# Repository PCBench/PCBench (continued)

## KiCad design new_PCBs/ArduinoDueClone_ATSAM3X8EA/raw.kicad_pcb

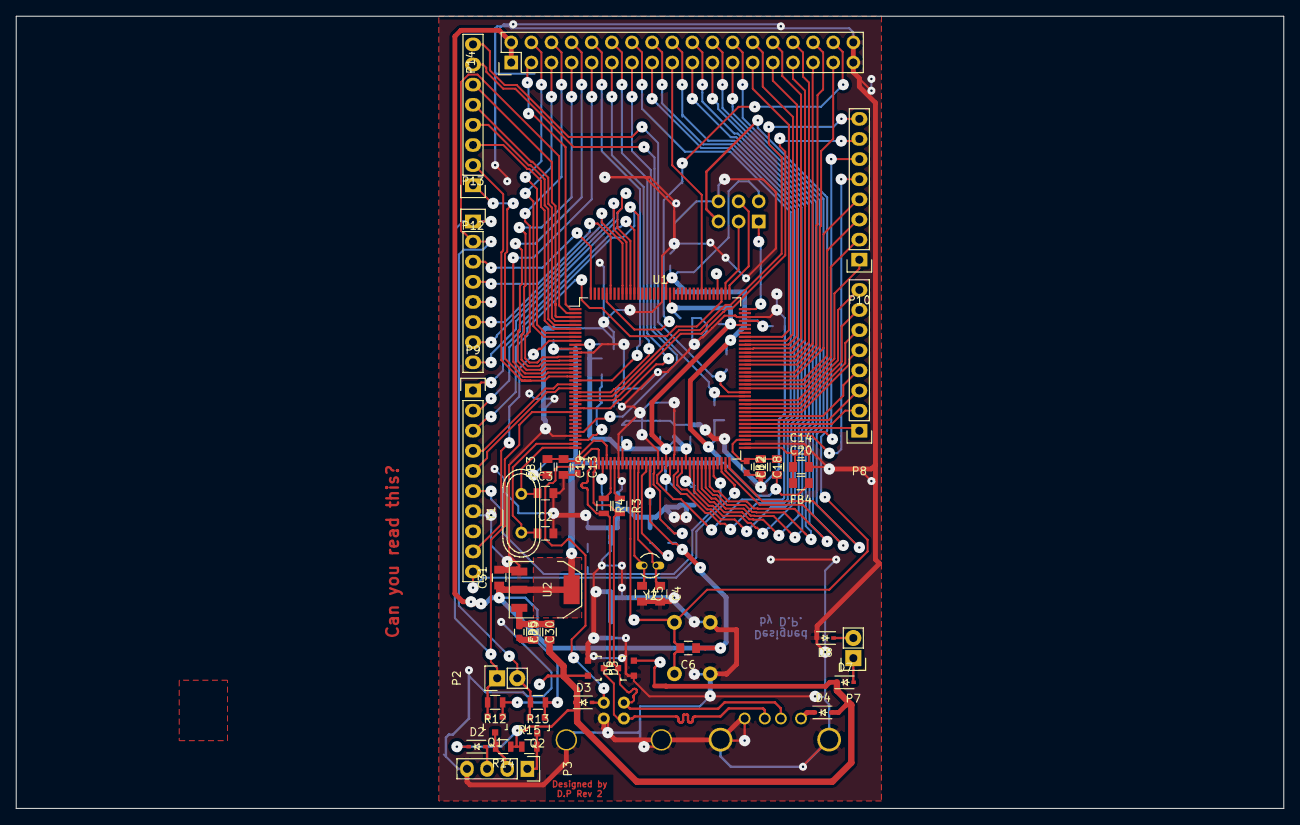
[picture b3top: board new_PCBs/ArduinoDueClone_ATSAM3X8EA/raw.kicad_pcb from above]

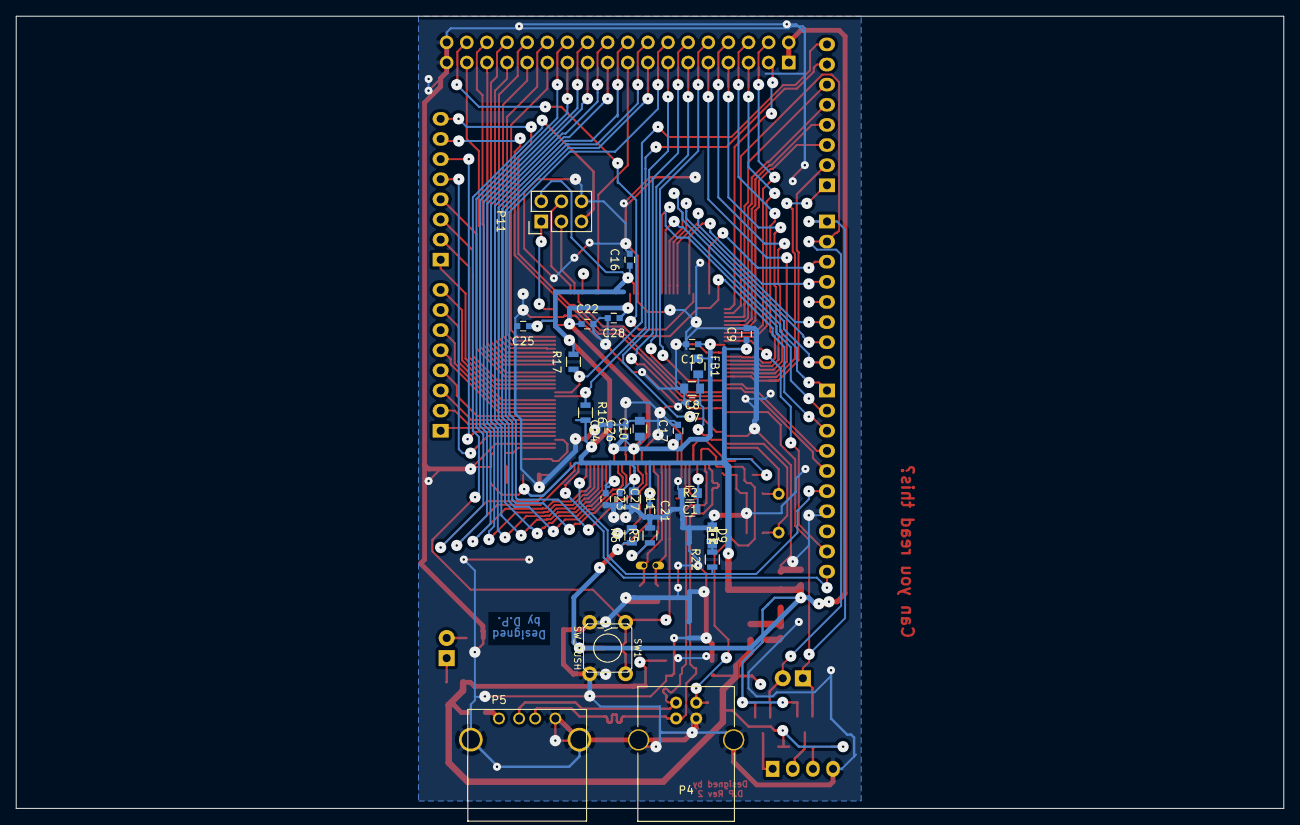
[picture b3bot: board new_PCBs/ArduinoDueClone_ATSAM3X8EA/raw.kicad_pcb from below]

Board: 2 copper layers, 160.0 x 100.0 mm, 75 parts (29 on the bottom side), 105 nets.

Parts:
C1, C2, C3, C4, C5: 22p; C_0805
C6: 10n; C_0805
C7, C9, C12, C13, C14, C15, C16, C17, C21, C22, C23, C24, C25, C26, C27, C28, C29: 100n; C_0603
C8, C10, C11, C18, C19, C20, C30, C31: 10u; C_0805
D2, D3, D4, D7, D8: PMEG2010AEH; SOD-323
D5, D6: BAV99; SOT-23
D9: LED; LED-0805
FB1, FB2, FB3, FB4, FB5: MH2029-300Y; C_0805
P2: 3.3V Serial; Pin_Header_Straight_1x02
P3: 5V_Serial; Pin_Header_Straight_1x04
P4: USB_B
P5: USB_A
P7: 5V_Power; Pin_Header_Straight_1x02
P8: ADCL; Pin_Header_Straight_1x08
P9: PWMH; Pin_Header_Straight_1x10
P10: ADCH; Pin_Header_Straight_1x08
P11: SPI; Pin_Header_Straight_2x03
P12: Communication; Pin_Header_Straight_1x08
P13: PWML; Pin_Header_Straight_1x08
P14: CONN_02X18; Pin_Header_Straight_2x18
Q1, Q2: BSS138; SOT-23
R2: 6k8 1%; R_0805
R3, R4: 39R 1%; R_0805
R5: NC; R_0805
R6: 100k; R_0805
R12, R13, R14, R15: 10k; R_0805
R16, R17: 1k5; R_0805
R22: 330; R_0805
SW1: SW_PUSH; 6MM_PushButton
U1: ATSAM3X8EA-AU; LQFP-144_20x20mm_Pitch0.5mm
U2: LD1117S33TR; SOT-223
Y1: 12MHz; Crystal_HC49-U_Vertical
Y2: 32.768Khz; Crystal_Round_Vertical_3mm_BigPad

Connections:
3.3V: C6.1, C9.1, C11.1, C16.1, C21.1, C23.1, C25.1, C27.1, C31.1, FB2.1, FB3.1, FB4.1, P11.2, P14.1, P14.2, Q1.1, Q2.1, R6.1, R12.1, R13.1, R16.2, R17.2, U1.11, U1.52, U1.57, U1.62, U1.105, U1.125, U2.2
/ATSAM3X8EA-AU/ADCREF: C12.1, C18.1, FB2.2, U1.75
/ATSAM3X8EA-AU/D+: D5.3, P4.3, P5.3, R4.2, U1.37
/ATSAM3X8EA-AU/D-: D6.3, P4.2, P5.2, R3.2, U1.38
/ATSAM3X8EA-AU/HSD+: R4.1, U1.42
/ATSAM3X8EA-AU/HSD-: R3.1, U1.43
/ATSAM3X8EA-AU/PA0: P10.8, U1.23
/ATSAM3X8EA-AU/PA1: P10.7, U1.24
/ATSAM3X8EA-AU/PA2: P8.8, U1.85
/ATSAM3X8EA-AU/PA3: P8.7, U1.84
/ATSAM3X8EA-AU/PA4: P8.6, U1.83
/ATSAM3X8EA-AU/PA6: P8.5, U1.82
/ATSAM3X8EA-AU/PA7: P14.12, U1.26
/ATSAM3X8EA-AU/PA10: P12.6, U1.3
/ATSAM3X8EA-AU/PA11: P12.5, U1.4
/ATSAM3X8EA-AU/PA12: P12.4, U1.5
/ATSAM3X8EA-AU/PA13: P12.3, U1.6
/ATSAM3X8EA-AU/PA14: P14.4, U1.7
/ATSAM3X8EA-AU/PA15: P14.5, U1.8
/ATSAM3X8EA-AU/PA16: P8.1, U1.78
/ATSAM3X8EA-AU/PA17: P9.9, U1.9
/ATSAM3X8EA-AU/PA18: P9.10, U1.70
/ATSAM3X8EA-AU/PA19: P14.23, U1.71
/ATSAM3X8EA-AU/PA20: P14.24, U1.72
/ATSAM3X8EA-AU/PA22: P8.4, U1.81
/ATSAM3X8EA-AU/PA23: P8.3, U1.80
/ATSAM3X8EA-AU/PA24: P8.2, U1.79
/ATSAM3X8EA-AU/PA25: P11.1, U1.108
/ATSAM3X8EA-AU/PA26: P11.4, U1.109
/ATSAM3X8EA-AU/PA27: P11.3, U1.110
/ATSAM3X8EA-AU/PA28: P9.3, U1.111
/ATSAM3X8EA-AU/PA29: P13.5, U1.112
/ATSAM3X8EA-AU/PB12: P12.7, R16.1, U1.86
/ATSAM3X8EA-AU/PB13: P12.8, R17.1, U1.87
/ATSAM3X8EA-AU/PB14: P14.34, U1.140
/ATSAM3X8EA-AU/PB15: P10.5, U1.76
/ATSAM3X8EA-AU/PB16: P10.6, U1.77
/ATSAM3X8EA-AU/PB17: P10.1, U1.88
/ATSAM3X8EA-AU/PB18: P10.2, U1.89
/ATSAM3X8EA-AU/PB19: P10.3, U1.90
/ATSAM3X8EA-AU/PB20: P10.4, U1.91
/ATSAM3X8EA-AU/PB21: P14.33, U1.92
/ATSAM3X8EA-AU/PB25: P13.3, U1.144
/ATSAM3X8EA-AU/PB26: P14.3, U1.1
/ATSAM3X8EA-AU/PB27: P9.6, R22.1, U1.68
/ATSAM3X8EA-AU/PC1: P14.14, U1.55
/ATSAM3X8EA-AU/PC2: P14.15, U1.59
/ATSAM3X8EA-AU/PC3: P14.16, U1.60
/ATSAM3X8EA-AU/PC4: P14.17, U1.116
/ATSAM3X8EA-AU/PC5: P14.18, U1.63
/ATSAM3X8EA-AU/PC6: P14.19, U1.64
/ATSAM3X8EA-AU/PC7: P14.20, U1.65
/ATSAM3X8EA-AU/PC8: P14.21, U1.66
/ATSAM3X8EA-AU/PC9: P14.22, U1.67
/ATSAM3X8EA-AU/PC12: P14.32, U1.94
/ATSAM3X8EA-AU/PC13: P14.31, U1.95
/ATSAM3X8EA-AU/PC14: P14.30, U1.96
/ATSAM3X8EA-AU/PC15: P14.29, U1.97
/ATSAM3X8EA-AU/PC16: P14.28, U1.98
/ATSAM3X8EA-AU/PC17: P14.27, U1.99
/ATSAM3X8EA-AU/PC18: P14.26, U1.100
/ATSAM3X8EA-AU/PC19: P14.25, U1.101
/ATSAM3X8EA-AU/PC21: P9.2, U1.132
/ATSAM3X8EA-AU/PC22: P9.1, U1.133
/ATSAM3X8EA-AU/PC23: P13.8, U1.134
/ATSAM3X8EA-AU/PC24: P13.7, U1.135
/ATSAM3X8EA-AU/PC25: P13.6, U1.136
/ATSAM3X8EA-AU/PC28: P13.4, U1.139
/ATSAM3X8EA-AU/PD0: P14.6, U1.13
/ATSAM3X8EA-AU/PD1: P14.7, U1.14
/ATSAM3X8EA-AU/PD2: P14.8, U1.15
/ATSAM3X8EA-AU/PD3: P14.9, U1.16
/ATSAM3X8EA-AU/PD4: P12.1, U1.17
/ATSAM3X8EA-AU/PD5: P12.2, U1.18
/ATSAM3X8EA-AU/PD6: P14.10, U1.19
/ATSAM3X8EA-AU/PD7: P9.4, U1.20
/ATSAM3X8EA-AU/PD8: P9.5, U1.21
/ATSAM3X8EA-AU/PD9: P14.11, U1.22
/ATSAM3X8EA-AU/PD10: P14.13, U1.32
/ATSAM3X8EA-AU/RX: P2.1, P13.1, Q1.2, R12.2, U1.27
/ATSAM3X8EA-AU/TX: P2.2, P13.2, Q2.2, R13.2, U1.2
/ATSAM3X8EA-AU/VBUS: D3.2, P4.1, U1.39
/ATSAM3X8EA-AU/VDDANA: C14.1, C20.1, FB4.2, U1.73
/ATSAM3X8EA-AU/VDDOUT: C10.1, C15.1, C17.1, C22.1, C24.1, C26.1, C28.1, FB1.1, U1.10, U1.45, U1.56, U1.61, U1.104, U1.124
/ATSAM3X8EA-AU/VDDOUTMI: C13.1, C19.1, FB3.2, U1.41
/Connections/MASTER_RESET: C6.2, P11.5, SW1.1, U1.47
/Power/5V: D2.1, D3.1, D4.2, D5.2, D6.2, D7.1, FB5.1, R14.1, R15.1
/Serial/RX_5V: P3.2, Q1.3, R14.2
/Serial/TX_5V: P3.1, Q2.3, R15.2
/Serial/VCC_SERIAL: D2.2, P3.3
GND: C1.2, C2.2, C3.2, C4.2, C5.2, C7.2, C8.2, C9.2, C10.2, C11.2, C12.2, C13.2, C14.2, C15.2, C16.2, C17.2, C18.2, C19.2, C20.2, C21.2, C22.2, C23.2, C24.2, C25.2, C26.2, C27.2, C28.2, C31.2, D5.1, D6.1, D8.2, D9.1, P3.4, P4.4, P4.5, P5.4, P5.5, P9.7, P11.6, P14.35, P14.36, R2.1, R5.2, SW1.2, U1.12, U1.33, U1.44, U1.54, U1.58, U1.74, U1.106, U1.126, U2.1
unnamed: C1.1, R2.2, U1.40
unnamed: C2.1, U1.35, Y1.1
unnamed: C3.1, U1.36, Y1.2
unnamed: C4.1, U1.49, Y2.1
unnamed: C5.1, U1.48, Y2.2
unnamed: C7.1, C8.1, FB1.2, U1.34
unnamed: C29.1, C30.1, FB5.2, U2.3
unnamed: C29.2, C30.2
unnamed: D4.1, P5.1
unnamed: D7.2, P7.1
unnamed: D8.1, P7.2
unnamed: D9.2, R22.2
unnamed: R5.1, U1.51
unnamed: R6.2, U1.53

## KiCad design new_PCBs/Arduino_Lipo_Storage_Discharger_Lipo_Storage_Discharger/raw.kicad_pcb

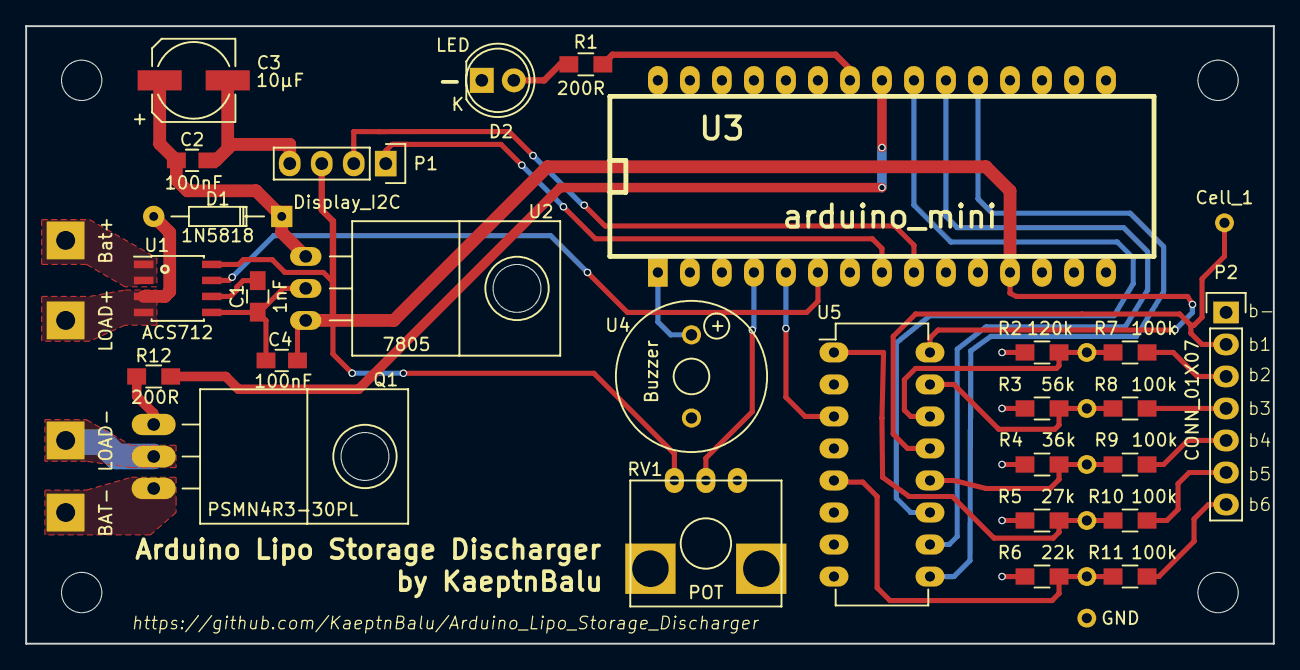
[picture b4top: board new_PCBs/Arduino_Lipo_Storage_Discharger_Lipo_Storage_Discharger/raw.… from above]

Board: 2 copper layers, 99.0 x 49.0 mm, 33 parts (0 on the bottom side), 31 nets.

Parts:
C1: 1nF; C_0805_HandSoldering
C2, C4: 100nF; C_0805_HandSoldering
C3: 10µF; c_elec_6.3x5.3
Cell_1: T1; Measurement_Point_Round-TH_Small
D1: 1N5818; Diode_DO-35_SOD27_Horizontal_RM10
D2: LED; LED-5MM
P1: Display_I2C; Socket_Strip_Straight_1x04
P2: CONN_01X07; Pin_Header_Straight_1x07
Q1: PSMN4R3-30PL; TO-220_Neutral123_Horizontal_LargePads
R1, R12: 200R; R_0805_HandSoldering
R2: 120k; R_0805_HandSoldering
R3: 56k; R_0805_HandSoldering
R4: 36k; R_0805_HandSoldering
R5: 27k; R_0805_HandSoldering
R6: 22k; R_0805_HandSoldering
R7, R8, R9, R10, R11: 100k; R_0805_HandSoldering
RV1: POT; RK09K1130A5R
U1: ACS712; SOIC-8_3.9x4.9mm_Pitch1.27mm
U2: 7805; TO-220_7805_Horizontal
U3: arduino_mini
U4: Buzzer; Buzzer_12x8.2_RM6.6
U5: 4051; DIP-16_W7.62mm_LongPads
W1: LOAD+; Measurement_Point_Square-TH_Big
W2: Bat+; Measurement_Point_Square-TH_Big
W3: LOAD-; Measurement_Point_Square-TH_Big
W4: BAT-; Measurement_Point_Square-TH_Big
W5: GND; Measurement_Point_Round-TH_Small

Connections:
/Cell_1: Cell_1.1, P2.2, U5.13
/Cell_2: R2.1, R7.2, U5.14
/Cell_3: R3.1, R8.2, U5.15
/Cell_4: R4.1, R9.2, U5.12
/Cell_5: R5.1, R10.2, U5.1
/Cell_6: R6.1, R11.2, U5.5
A1: U3.5, U5.3
A2: U1.7, U3.6
Bat+: U1.1, U1.2, W2.1
Bat-: C1.1, C2.2, C3.2, C4.2, D2.1, P1.4, P2.1, Q1.3, R2.2, R3.2, R4.2, R5.2, R6.2, RV1.1, U1.5, U2.GND, U3.14, U3.19, U4.2, U5.8, W4.1, W5.1
D2: U3.20, U5.9
D3: U3.21, U5.10
D4: U3.22, U5.11
D6: R1.2, U3.24
D13: U3.1, U4.1
Input+: D1.2, U1.3, U1.4, W1.1
LOAD-: Q1.2, W3.1
unnamed: C1.2, U1.6
unnamed: C2.1, C3.1, D1.1, U2.VI
unnamed: D2.2, R1.1
unnamed: P2.3, R7.1
unnamed: P2.4, R8.1
unnamed: P2.5, R9.1
unnamed: P2.6, R10.1
unnamed: P2.7, R11.1
unnamed: Q1.1, R12.2
unnamed: R12.1, U3.23
unnamed: RV1.2, U3.4
SCL: P1.2, U3.9
SDA: P1.1, U3.8
VCC: C4.1, P1.3, RV1.3, U1.8, U2.VO, U3.12, U5.16

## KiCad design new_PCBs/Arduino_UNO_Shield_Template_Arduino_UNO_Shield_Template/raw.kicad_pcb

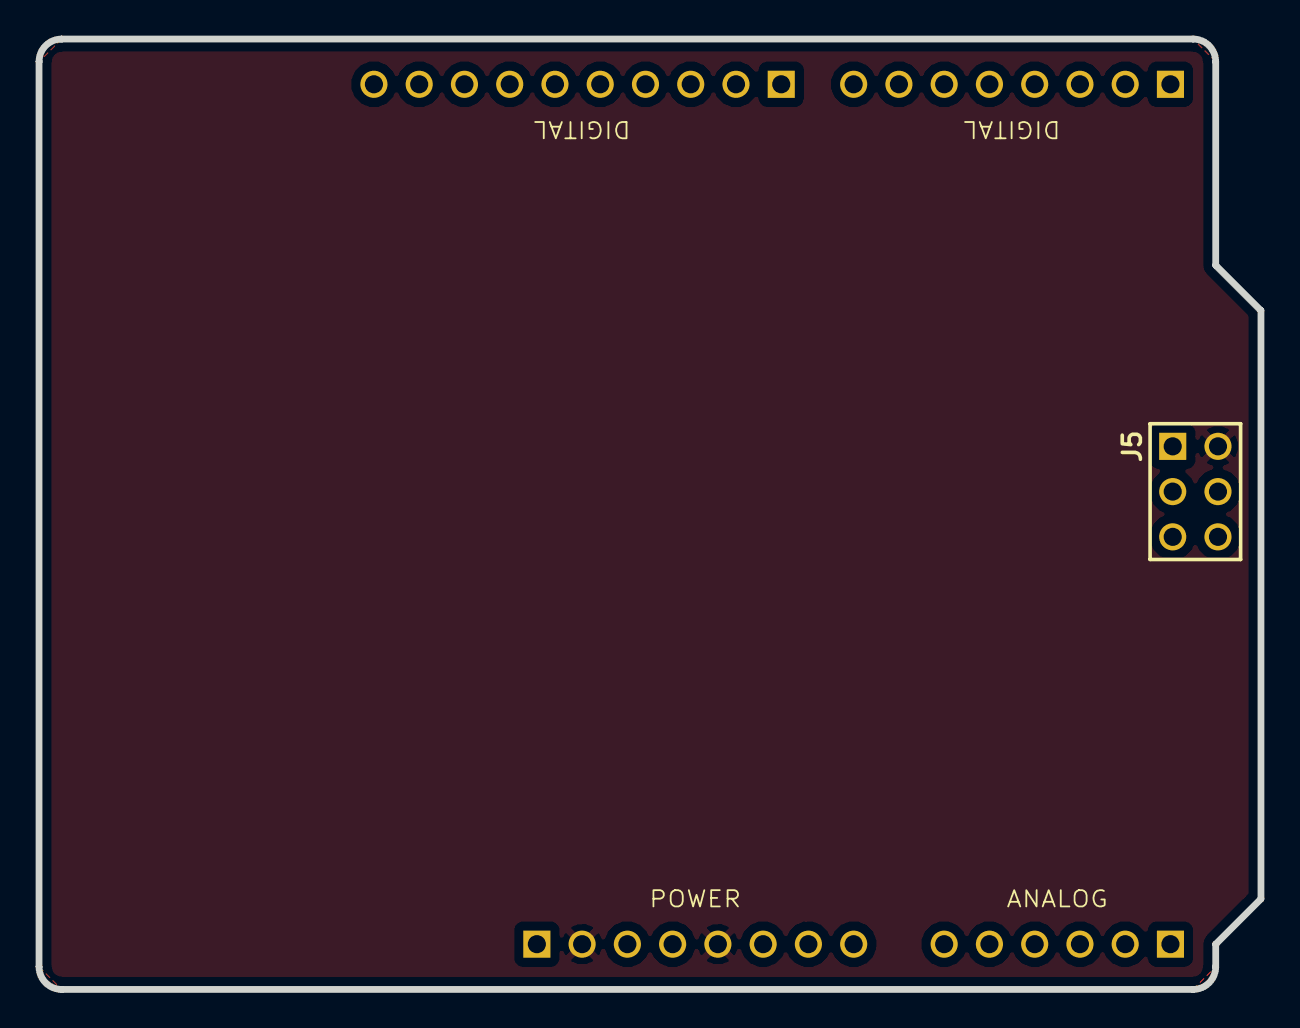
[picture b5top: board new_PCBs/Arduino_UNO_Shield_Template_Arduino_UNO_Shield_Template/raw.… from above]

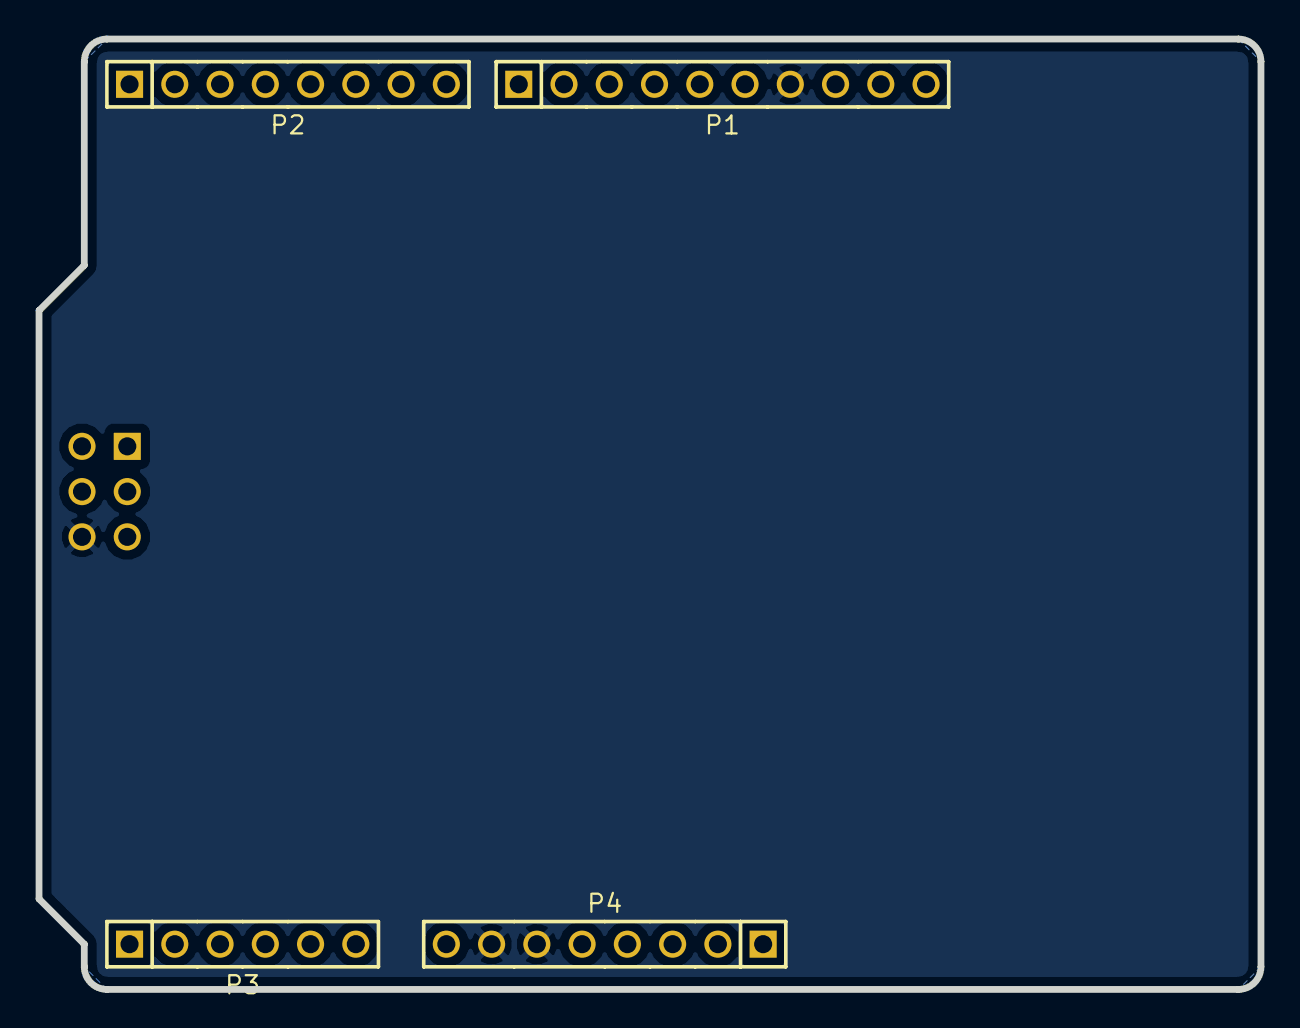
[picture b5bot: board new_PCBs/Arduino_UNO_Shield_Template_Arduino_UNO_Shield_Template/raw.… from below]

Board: 2 copper layers, 68.6 x 53.3 mm, 5 parts (4 on the bottom side), 8 nets, no tracks yet.

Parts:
J5: HEADER_F_2.54MM_2R6P_ST_AU_PTH; HEADER_F_100MIL_2R6P_ST_GOLD_PTH
P1: HEADER_M_2.54MM_1R10P_ST_AU_PTH
P2, P4: HEADER_M_2.54MM_1R8P_ST_AU_PTH
P3: HEADER_M_2.54MM_1R6P_ST_AU_PTH

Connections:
5V: J5.2, P4.2, P4.5
AD4/SDA: P1.9, P3.5
AD5/SCL: P1.10, P3.6
GND: J5.6, P1.7, P4.6, P4.7
IO11/MOSI: J5.4, P1.4
IO12/MISO: J5.1, P1.5
IO13/SCK: J5.3, P1.6
RESET: J5.5, P4.3

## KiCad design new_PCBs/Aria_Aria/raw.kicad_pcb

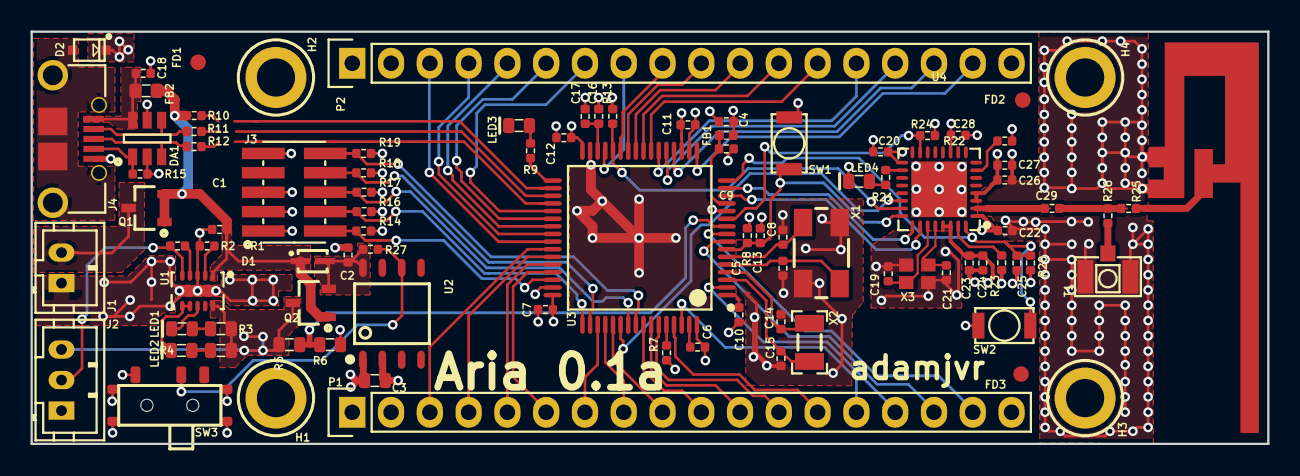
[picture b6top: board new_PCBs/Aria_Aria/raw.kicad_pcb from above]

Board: 4 copper layers, 81.0 x 27.0 mm, 92 parts (0 on the bottom side), 84 nets.

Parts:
ANT1: Inverted_F_PCB_Antenna; PCB_IF_ANT_2.4G
C1, C2: CL05A105KA5NQNC; C0402
C3: CL10A106KQ8NNNC; C0603
C4, C6, C7, C9, C10, C11, C12, C13, C17, C18, C20, C22, C23, C24, C25, C26, C27, C28: CL05B104JP5NNNC; C0402
C5, C8, C19, C21: CL05C090CB5NNNC; C0402
C14, C15: CL05C180GB5NCNC; C0402
C16: CL05A475KQ5NRNC; C0402
C29: 600L5R6BT200T; C0402
D1: BAT20JFILM
D2: RSB39VTE-17
DA1: ESDA6V1BC6
FB1: BLM15HG601SN1D
FB2: MI0603K300R-10
FD1, FD2, FD3: FIDUCIAL
H1, H2, H3, H4: M2.5_Hole; M2.5_HOLE
J1: B2B-PH-K-S(LF)(SN)
J2: B3B-PH-K-S(LF)(SN)
J3: 20021121-00010C4LF
J4: 0475890001-MicroUSBPort; 0475890001
LED1: LTST-C191KGKT; LED0603
LED2: LTST-C191KFKT; LED0603
LED3, LED4: LTST-C193TBKT-5A; LED0603
P1, P2: CONN_01X18; Socket_Strip_Straight_1x18
Q1, Q2: DMG2307L-7
R1: RC1005F4870CS; R0402
R2, R8, R9, R14, R16, R17, R18, R19, R20, R21: RC1005F102CS; R0402
R3, R4: RC1608J202CS; R0603
R5, R6: ERA-3AEB3741V; R0603
R7, R10, R13, R24, R27: RC1005F103CS; R0402
R11, R12: CPF0402B22RE1; R0402
R15: RC1005J473CS; R0402
R22, R23: RC1005F123CS; R0402
R25, R26: ERJ-2GE0R00X; R0402
SW1, SW2: B3U-1000P
SW3: CUS-12TB
T1: 1909763-1
U1: BQ24210DQCT; BQ24210
U2: TC1265-3.3VOA
U3: STM32F446RET6_-_TQFP64; STM32F446RET6
U4: ESP8285
X1: ABM3B8.000MHZB2T
X2: ABS07-32.768KHZ-9-T
X3: FA-128_26.0000MF10Z-AC3

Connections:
+3V3: C3.1, C4.1, C6.1, C7.1, C10.1, C11.1, C12.1, C20.1, C22.1, C23.1, C24.1, C26.1, C27.1, C28.1, FB1.1, J3.1, P1.2, P2.2, R8.1, R13.1, R14.1, R16.1, R17.1, R18.1, R19.1, R20.2, R22.2, R24.1, U2.1, U3.1, U3.19, U3.32, U3.48, U3.64, U4.1, U4.3, U4.4, U4.11, U4.17, U4.29, U4.30
/MCU_STM32F446RET6/BAT_VOLT: R5.2, R6.1, U3.10
/MCU_STM32F446RET6/ESPTOST_BOOT0: U3.54, U4.22
/MCU_STM32F446RET6/ESPTOST_BOOT1: R13.2, U3.28, U4.23
/MCU_STM32F446RET6/ESP_PGM_MODE: R24.2, U3.11, U4.15
/MCU_STM32F446RET6/ESP_ST_RST: C13.1, R8.2, SW1.1, U3.7, U4.24
/MCU_STM32F446RET6/ESP_URX: U3.14, U4.26
/MCU_STM32F446RET6/ESP_UTX: U3.15, U4.25
/MCU_STM32F446RET6/HEARTBEAT: R9.1, U3.33
/MCU_STM32F446RET6/NJTRST: J3.10, R19.2, U3.56
/MCU_STM32F446RET6/PA3: P2.17, U3.17
/MCU_STM32F446RET6/PA4: P2.16, U3.20
/MCU_STM32F446RET6/PA5: P2.15, U3.21
/MCU_STM32F446RET6/PA6: P2.14, U3.22
/MCU_STM32F446RET6/PA7: P2.13, U3.23
/MCU_STM32F446RET6/PA8: P2.3, U3.41
/MCU_STM32F446RET6/PA9: P1.3, U3.42
/MCU_STM32F446RET6/PA10: P1.4, U3.43
/MCU_STM32F446RET6/PA11: P1.5, U3.44
/MCU_STM32F446RET6/PA12: P1.6, U3.45
/MCU_STM32F446RET6/PB0: P2.10, U3.26
/MCU_STM32F446RET6/PB1: P2.9, U3.27
/MCU_STM32F446RET6/PB5: P1.10, U3.57
/MCU_STM32F446RET6/PB6: P1.11, U3.58
/MCU_STM32F446RET6/PB7: P1.12, U3.59
/MCU_STM32F446RET6/PB8: P1.13, U3.61
/MCU_STM32F446RET6/PB9: P1.14, U3.62
/MCU_STM32F446RET6/PB10: P2.8, U3.29
/MCU_STM32F446RET6/PC0: P1.16, U3.8
/MCU_STM32F446RET6/PC1: P1.17, U3.9
/MCU_STM32F446RET6/PC4: P2.12, U3.24
/MCU_STM32F446RET6/PC5: P2.11, U3.25
/MCU_STM32F446RET6/PC6: P2.7, U3.37
/MCU_STM32F446RET6/PC7: P2.6, U3.38
/MCU_STM32F446RET6/PC8: P2.5, U3.39
/MCU_STM32F446RET6/PC9: P2.4, U3.40
/MCU_STM32F446RET6/PC10: P1.7, U3.51
/MCU_STM32F446RET6/PC11: P1.8, U3.52
/MCU_STM32F446RET6/PC12: P1.9, U3.53
/MCU_STM32F446RET6/PC13: P1.15, U3.2
/MCU_STM32F446RET6/STM_ESP_RST: C25.1, R20.1, SW2.2, U3.16, U4.32
/MCU_STM32F446RET6/SWCLK_TCK: J3.4, R16.2, U3.49
/MCU_STM32F446RET6/SWDIO_TMS: J3.2, R14.2, U3.46
/MCU_STM32F446RET6/SWO_TDI: J3.8, R18.2, U3.50
/MCU_STM32F446RET6/SWO_TDO: J3.6, R17.2, U3.55
/MCU_STM32F446RET6/VBUS: C1.1, D1.1, FB2.1, Q1.1, Q1.2, Q2.1, R10.2, U1.1
/Power/BAT: J2.3, Q2.3, R3.2, R4.2, R5.1, U1.10
/Power/LDO_VIN: C2.1, D1.2, Q2.2, R27.1, U2.8
/Power/THERM: J2.2, R2.2, U1.5
/WiFi-ESP8285/ANTENNA: C29.2, R25.1, R26.1
/WiFi-ESP8285/ANT_F: ANT1.1, R25.2
/WiFi-ESP8285/ANT_UM: R26.2, T1.1
/WiFi-ESP8285/LNA: C29.1, U4.2
GND: ANT1.2, C1.2, C2.2, C3.2, C4.2, C5.2, C6.2, C7.2, C8.2, C9.2, C10.2, C11.2, C12.2, C13.2, C14.2, C15.2, C16.2, C17.2, C18.1, C19.2, C20.2, C21.2, C22.2, C23.2, C24.2, C25.2, C26.2, C27.2, C28.2, D2.2, DA1.2, DA1.5, J1.1, J2.1, J3.3, J3.5, J3.9, J4.5, LED3.2, LED4.2, P1.1, P1.18, P2.1, P2.18, R1.2, R6.2, R7.2, R15.2, R23.1, SW1.2, SW2.1, SW3.1, SW3.4, T1.2, U1.3, U1.11, U2.2, U3.12, U3.18, U3.31, U3.47, U3.63, U4.33, X1.2, X1.4, X3.2, X3.4
unnamed: C5.1, U3.5, X1.1
unnamed: C8.1, U3.6, X1.3
unnamed: C9.1, FB1.2, U3.13
unnamed: C14.1, U3.4, X2.1
unnamed: C15.1, U3.3, X2.2
unnamed: C16.1, C17.1, U3.30
unnamed: C18.2, DA1.6, FB2.2, J4.1
unnamed: C19.1, U4.27, X3.1
unnamed: C21.1, U4.28, X3.3
unnamed: D2.1, J4.6, J4.7, J4.8, J4.9, J4.10, J4.11
unnamed: DA1.1, J4.4, R15.1
unnamed: DA1.3, J4.3, R12.2
unnamed: DA1.4, J4.2, R11.2
unnamed: J1.2, Q1.3
unnamed: LED1.1, R3.1
unnamed: LED1.2, U1.8
unnamed: LED2.1, R4.1
unnamed: LED2.2, U1.6, U1.7
unnamed: LED3.1, R9.2
unnamed: LED4.1, R21.2
unnamed: R1.1, U1.2
unnamed: R2.1, U1.4
unnamed: R7.1, U3.60
unnamed: R10.1, U3.34
unnamed: R11.1, U3.35
unnamed: R12.1, U3.36
unnamed: R21.1, U4.18
unnamed: R22.1, U4.7
unnamed: R23.2, U4.31
unnamed: R27.2, SW3.2, U2.6
